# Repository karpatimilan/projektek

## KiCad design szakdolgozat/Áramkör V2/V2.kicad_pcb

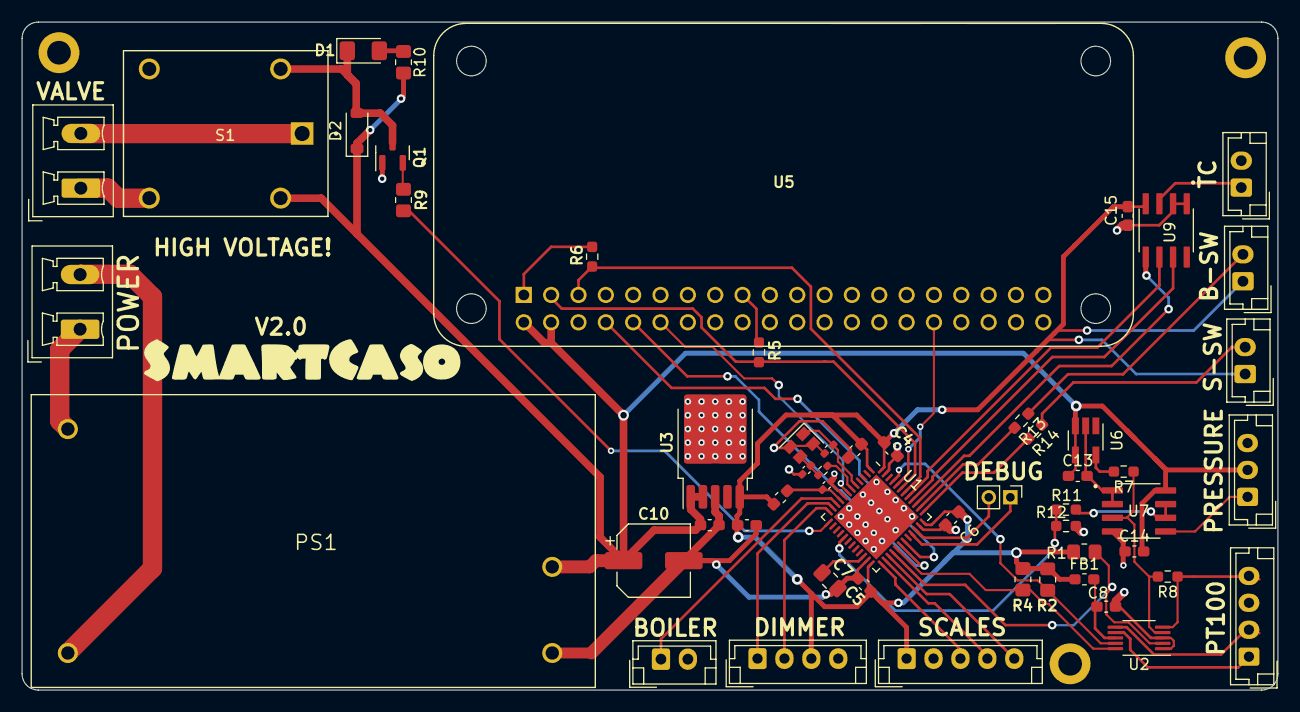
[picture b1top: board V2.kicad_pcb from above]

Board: 2 copper layers, 116.7 x 62.1 mm, 58 parts (1 on the bottom side), 52 nets.

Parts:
C1, C4, C5, C6, C8, C14: 100nF; C_0603_1608Metric_Pad1.08x0.95mm_HandSolder
C2, C3: 10pF; C_0402_1005Metric_Pad0.74x0.62mm_HandSolder
C7: 2.2uF; C_0805_2012Metric_Pad1.18x1.45mm_HandSolder
C9: 100nF; C_0402_1005Metric_Pad0.74x0.62mm_HandSolder
C10: C_Polarized_Small; CP_Elec_6.3x9.9
C11: 1uF; C_0603_1608Metric_Pad1.08x0.95mm_HandSolder
C12, C13: 47uF; C_0603_1608Metric_Pad1.08x0.95mm_HandSolder
C15: 0.1uF; C_0603_1608Metric_Pad1.08x0.95mm_HandSolder
D1: LED; LED_1206_3216Metric_Pad1.42x1.75mm_HandSolder
D2: 1N4148; D_SOD-123
FB1, FB2: FerriteBead; L_0603_1608Metric_Pad1.05x0.95mm_HandSolder
H1, H2, H3: MountingHole; MountingHole_2.2mm_M2_DIN965_Pad
J1: PT100; JST_EH_B4B-EH-A_1x04_P2.50mm_Vertical
J2: POWER; PhoenixContact_MCV_1,5_2-G-5.08_1x02_P5.08mm_Vertical
J3: VALVE; PhoenixContact_MCV_1,5_2-G-5.08_1x02_P5.08mm_Vertical
J4: THERMOCOUPLE; JST_EH_B2B-EH-A_1x02_P2.50mm_Vertical
J5: BOILER; JST_EH_B2B-EH-A_1x02_P2.50mm_Vertical
J6: Pressure; JST_EH_B3B-EH-A_1x03_P2.50mm_Vertical
J7: SCALES; JST_EH_B5B-EH-A_1x05_P2.50mm_Vertical
J8: DIMMER; JST_EH_B4B-EH-A_1x04_P2.50mm_Vertical
J9: DEBUG; PinHeader_1x02_P2.00mm_Vertical
J10: BREW_SWITCH; JST_EH_B2B-EH-A_1x02_P2.50mm_Vertical
J11: STEAM_SWITCH; JST_EH_B2B-EH-A_1x02_P2.50mm_Vertical
PS1: IRM-15-5; CONV_IRM-15-5
Q1: S8050; SOT-23
R1, R2, R4: 10K; R_0805_2012Metric_Pad1.20x1.40mm_HandSolder
R3: 0R; R_0402_1005Metric_Pad0.72x0.64mm_HandSolder
R5, R6, R7: 3.3K; R_0603_1608Metric_Pad0.98x0.95mm_HandSolder
R8: 100R; R_0603_1608Metric_Pad0.98x0.95mm_HandSolder
R9, R10: 1K; R_0805_2012Metric_Pad1.20x1.40mm_HandSolder
R11: 620; R_0603_1608Metric_Pad0.98x0.95mm_HandSolder
R12: 330; R_0603_1608Metric_Pad0.98x0.95mm_HandSolder
R13, R14: 1K; R_0603_1608Metric_Pad0.98x0.95mm_HandSolder
S1: JQC-3FF-S-Z; SW_JQC-3FF-S-Z
U1: STM32F411CEUx; QFN-48-1EP_7x7mm_P0.5mm_EP5.6x5.6mm
U2: ADS1115IDGST; VSSOP-10_3x3mm_P0.5mm
U3: TPS7B8633QKVURQ1; TO-252-5_TabPin6
U5: RASPBERRY_PI_ZERO_2_W; MODULE_RASPBERRY_PI_ZERO_2_W
U6: PREF4132B33DBVRQ1; SOT-23-5_HandSoldering
U7: LMC6482AIMX_NOPB; LMC6482
U9: MAX6675ISA_; MAX6675
Y1: 25 Mhz; Oscillator_SMD_SeikoEpson_SG210-4Pin_2.5x2.0mm

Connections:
+5V: C10.1, C11.1, C13.1, C14.2, D2.1 (K), J6.2, PS1.+V, R10.1, S1.5, U3.1 (VI), U3.2 (EN), U5.2 (5V_2), U5.4 (5V_4), U6.3 (EN), U6.4 (VIN), U7.8 (V+)
/3.3V: C1.1, C4.1, C5.1, C6.1, C12.1, C15.2, FB1.1, FB2.1, J7.1, J8.3, J10.1, J11.1, R1.2, R2.2, R4.2, U1.1 (VBAT), U1.24 (VDD), U1.36 (VDD), U1.48 (VDD), U3.5 (VO), U9.4 (VCC)
/+T: J4.1, U9.3 (T+)
/ALERT_RDY: R1.1, U1.28 (PB15), U2.2 (ALERT_RDY)
/AN0: R7.1, R8.2, U2.4 (AIN0), U7.3 (POSA)
/AN1: J1.4, R8.1, U2.5 (AIN1)
/AN2: J1.2, U2.6 (AIN2)
/AN3: J1.1, U2.7 (AIN3)
/BOILER_PWM: J5.1, U1.10 (PA0)
/Brew_Switch: R13.2, U1.38 (PA15)
/DIMMER_PWM: J8.1, U1.11 (PA1)
/HX711_1_DATA: J7.4, U1.26 (PB13)
/HX711_2_DATA: J7.5, U1.27 (PB14)
/HX711_SCK: J7.3, U1.25 (PB12)
/L: J3.1, S1.4
/MCU_OSC_IN: C2.2, U1.5 (PH0), Y1.1
/MCU_OSC_OUT: R3.1, U1.6 (PH1)
/NEGA: C13.2, U6.2 (GND), U7.1 (OUTA), U7.2 (NEGA)
/NEGB: R11.1, U7.6 (NEGB), U7.7 (OUTB)
/POSB: J6.1, U7.5 (POSB)
/POWER_L: J2.1, PS1.AC/L
/POWER_N: J2.2, PS1.AC/N
/RPI 3.3V: R5.2, R6.2, U5.1 (3V3_1), U5.17 (3V3_17)
/Relay: R9.2, U1.13 (PA3)
/STM32-ADS_SCL: R4.1, U1.29 (PA8), U2.10 (SCL)
/STM32-ADS_SDA: R2.1, U1.45 (PB8), U2.9 (SDA)
/STM32-MAX6675_CS: U1.41 (PB5), U9.6 (~CS)
/STM32-MAX6675_MISO: U1.40 (PB4), U9.7 (SO)
/STM32-MAX6675_SCK: U1.39 (PB3), U9.5 (SCK)
/STM32-RASPBERRY_SCL: R6.1, U1.42 (PB6), U5.5 (GPIO3/SCL)
/STM32-RASPBERRY_SDA: R5.1, U1.43 (PB7), U5.3 (GPIO2/SDA1)
/STM32_BOOT: U1.44 (BOOT0), U5.32 (GPIO12)
/STM32_RESET: U1.7 (NRST), U5.12 (GPIO18/GPIO_GEN1)
/STM32_RX-RPI_TX: U1.31 (PA10), U5.8 (GPIO14/TXD0)
/STM32_TX-RPI_RX: U1.30 (PA9), U5.10 (GPIO15/RXD0)
/SWCLK: J9.1, U1.33 (PA12)
/SWDIO: J9.2, U1.34 (PA13)
/Scaled_Pressure: R11.2, R12.1, U1.17 (PA7)
/Steam_Switch: R14.2, U1.37 (PA14)
/VREF: C9.1, FB2.2, U1.9 (VDDA)
/Valve: J3.2, S1.1
/XTAL_IN: C3.1, R3.2, Y1.3
/ZC_DIMMER: J8.2, U1.12 (PA2)
GND: C1.2, C2.1, C3.2, C4.2, C5.2, C6.2, C7.2, C8.2, C9.2, C10.2, C11.2, C12.2, C14.1, C15.1, J1.3, J4.2, J5.2, J6.3, J7.2, J8.4, PS1.-V, Q1.1 (E), R12.2, U1.8 (VSSA), U1.23 (VSS), U1.35 (VSS), U1.47 (VSS), U1.49 (VSS), U2.1 (ADDR), U2.3 (GND), U3.3 (GND), U5.6 (GND_6), U7.4 (V-), U9.1 (GND), U9.2 (T-), Y1.2, Y1.4
unnamed: D1.2 (A), R10.2
unnamed: D1.1 (K), D2.2 (A), Q1.3 (C), S1.2
unnamed: J10.2, R13.1
unnamed: J11.2, R14.1
unnamed: Q1.2 (B), R9.1
unnamed: C7.1, U1.22 (VCAP1)
unnamed: C8.1, FB1.2, U2.8 (VDD)
unnamed: R7.2, U6.5 (VREF)

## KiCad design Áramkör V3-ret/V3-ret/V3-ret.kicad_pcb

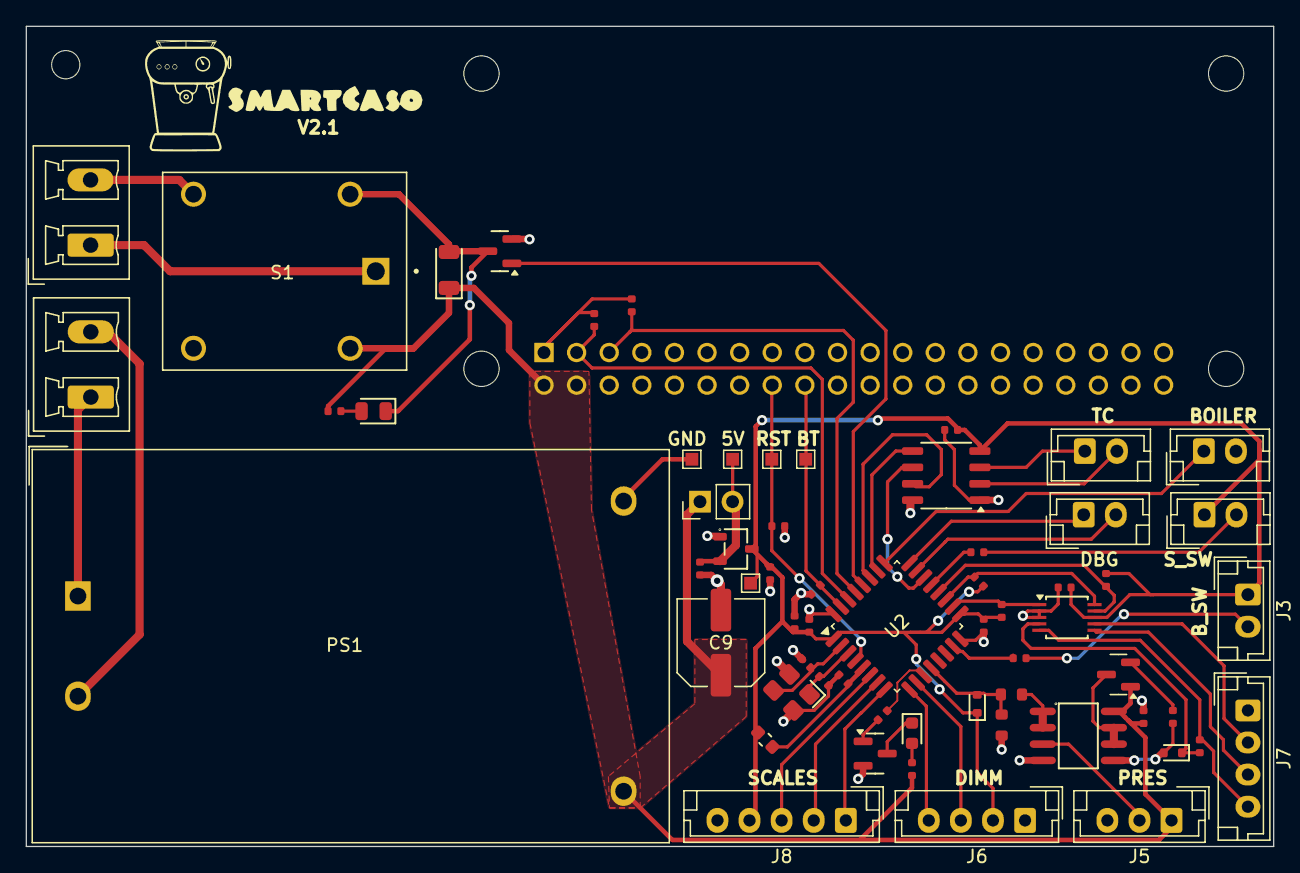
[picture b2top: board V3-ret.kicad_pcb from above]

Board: 2 copper layers, 97.2 x 63.9 mm, 64 parts (1 on the bottom side), 52 nets.

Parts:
5V1: TestPoint; TestPoint_Pad_1.0x1.0mm
C1, C5, C6, C11, C12, C13: 100nF; C_0402
C2, C3: 10pF; C_0402
C4, C8: 1uF; C_0402
C7: 4.7uF; C_0402
C9: C_Polarized; C_Elec_6.3x7.7
C10: 10nF; C_0402
D1: Green; D_0603
D2: Green; D_0805
D3: SM4007PL; D_SOD-123FL
D6, D7: 1SS389; D_SOD-523
FB1: FB_0603
GND1: TestPoint; TestPoint_Pad_1.0x1.0mm
H2: MountingHole; MountingHole_2.2mm_M2
J1, J2: Conn_01x02; PhoenixContact_MCV_1,5_2-G-5.08_1x02_P5.08mm_Vertical
J3, J4, J9, J11, J12: Conn_01x02; JST_EH_B2B-EH-A_1x02_P2.50mm_Vertical
J5: Conn_01x03; JST_EH_B3B-EH-A_1x03_P2.50mm_Vertical
J6, J7: Conn_01x04; JST_EH_B4B-EH-A_1x04_P2.50mm_Vertical
J8: Conn_01x05; JST_EH_B5B-EH-A_1x05_P2.50mm_Vertical
JPr1: Jumper_2_Open; PinHeader_1x02_P2.54mm_Vertical
PS1: HLK-10M05; Converter_ACDC_Hi-Link_HLK-10Mxx
Q1, Q2: 2N7002; Q_SOT-23
R1: 10kΩ; R_0402
R2: 100Ω; R_0402
R3, R4, R5, R15, R16: 1kΩ; R_0402
R6, R7, R8, R18, R19: 3.3kΩ; R_0402
R17: 820Ω; R_0603
R20: 300Ω; R_0603
R21: 2.4kΩ; R_0402
S1: JQC-3FF-S-Z; SW_JQC-3FF-S-Z
TP1, TP2, TP3: TestPoint; TestPoint_Pad_1.0x1.0mm
U1: XC6206P332MR; SOT-23-3_L2.9-W1.6-P1.90-LS2.8-BR
U2: STM32F301K8Tx; LQFP-32_7x7mm_P0.8mm
U3: MCP6002T; SOIC-8_L4.9-W3.9-P1.27-LS6.0-BL
U4: RASPBERRY_PI_ZERO_2_W; MODULE_RASPBERRY_PI_ZERO_2_W
U5: ADS1115IDGS; TSSOP-10_3x3mm_P0.5mm
U9: MCP1525-TT; SOT-23
U10: MAX6675ISA_; SOIC-8_3.9x4.9mm_P1.27mm
X1: X322525MOB4SI; OSC-SMD_4P-L3.2-W2.5-BL

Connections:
1mA_CURR_SRC: J7.4, R2.2, U5.5 (AIN1)
230V_L: J1.1, PS1.1 (AC/L)
230V_N: J1.2, PS1.2 (AC/N)
+3.3V: C5.1, C6.1, C7.1, C8.1, C11.1, C12.1, D6.1, FB1.2, J3.1, J4.1, J6.2, J8.4, R6.1, R7.1, R8.1, R18.2, R19.2, TP3.1, U1.3 (Vout), U2.1 (VDD), U2.17 (VDD), U4.1 (3V3_1), U4.17 (3V3_17), U5.8 (VDD), U10.4 (VCC)
+5V: C9.1, C13.1, D3.1, J5.1, JPr1.1 (A), PS1.4 (+Vout), R3.2, R5.1, S1.5, U3.8 (VDD), U4.2 (5V_2), U4.4 (5V_4), U9.1 (Vin)
/5V_JMPR: 5V1.1, C4.1, JPr1.2 (B), U1.2 (Vin)
/NEG_B: U3.6 (-INB), U3.7 (OUTB), U9.3 (Vss)
/POS_B: D7.2, R21.2, U3.5 (+INB)
ADC_SCL: R6.2, U2.19 (PA9), U5.10 (SCL)
ADC_SDA: R7.2, U2.20 (PA10), U5.9 (SDA)
ALERT_RDY: R8.2, U2.18 (PA8), U5.1 (ADDR)
AN0: D7.1, R2.1, U5.4 (AIN0)
AN2: J7.3, U5.6 (AIN2)
AN3: J7.2, U5.7 (AIN3)
BOILER_PWM: J9.1, U2.25 (PA15)
BOOT: R1.1, TP1.1, U2.31 (BOOT0), U4.18 (GPIO24/GPIO_GEN5)
BREW_SWITCH: R15.1, U2.15 (PB1)
DEBUG_CLK: J12.1, U2.24 (PA14)
DEBUG_SDA: J12.2, U2.23 (PA13)
DIMMER: J6.4, U2.9 (PA3)
DIMMER_ZC: J6.3, U2.10 (PA4)
GND: C1.1, C2.1, C3.1, C4.2, C5.2, C6.2, C7.2, C8.2, C9.2, C10.2, C11.2, C12.2, C13.2, GND1.1, J5.3, J6.1, J7.1, J8.5, J9.2, PS1.3 (-Vout), Q1.2 (S), Q2.2 (S), R1.2, R20.2, U1.1 (GND), U2.16 (VSS), U2.32 (VSS), U3.4 (-VSS), U4.6 (GND_6), U4.9 (GND_9), U4.14 (GND_14), U4.20 (GND_20), U4.25 (GND_25), U4.30 (GND_30), U4.34 (GND_34), U4.39 (GND_39), U5.2 (ALERT/RDY), U5.3 (GND), U10.1 (GND), U10.8 (N.C.), X1.2 (GND), X1.4 (GND)
HX711_D1: J8.2, U2.7 (PA1)
HX711_D2: J8.3, U2.6 (PA0)
HX711_SCL: J8.1, U2.8 (PA2)
LED: R4.1, U2.11 (PA5)
MAX6675_CS: U2.22 (PA12), U10.6 (~CS)
MAX6675_MISO: U2.27 (PB4), U10.7 (SO)
MAX6675_SCK: U2.26 (PB3), U10.5 (SCK)
unnamed: D1.2, R3.1
unnamed: D2.2, R5.2
unnamed: J3.2, R15.2
unnamed: J4.2, R16.2
unnamed: D2.1, D3.2, Q1.3 (D), S1.2
unnamed: D1.1, Q2.3 (D)
unnamed: Q2.1 (G), R4.2
unnamed: R17.1, U3.1 (OUTA), U3.2 (-INA)
unnamed: R21.1, U9.2 (Vout)
PRESSURE: J5.2, U3.3 (+INA)
RCC_OSC_IN: C2.2, U2.2 (PF0), X1.3 (OSC)
RCC_OSC_OUT: C3.2, U2.3 (PF1), X1.1 (OSC)
RELAY: Q1.1 (G), U2.28 (PB5)
RESET: C1.2, TP2.1, U2.4 (NRST), U4.16 (GPIO23/GPIO_GEN4)
RPI_SCL: R18.1, U2.29 (PB6), U4.5 (GPIO3/SCL)
RPI_SDA: R19.1, U2.30 (PB7), U4.3 (GPIO2/SDA1)
Relay_L1: J2.1, S1.1
Relay_L2: J2.2, S1.3
SCALED_PRESSURE: D6.2, R17.2, R20.1, U2.12 (PA6)
STEAM_SWITCH: R16.1, U2.21 (PA11)
T+: J11.1, U10.3 (T+)
T-: J11.2, U10.2 (T-)
VDDA: C10.1, FB1.1, U2.5 (VDDA)

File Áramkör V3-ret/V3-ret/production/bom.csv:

Designator,Footprint,Quantity,Value,LCSC Part #
"5V1, GND1, TP1, TP2, TP3",TestPoint_Pad_1.0x1.0mm,5,TestPoint,
"C1, C11, C12, C13, C5, C6",C_0402,6,100nF,C1525
C10,C_0402,1,10nF,C15195
"C2, C3",C_0402,2,10pF,C32949
"C4, C8",C_0402,2,1uF,C52923
C7,C_0402,1,4.7uF,C23733
C9,C_Elec_6.3x7.7,1,C_Polarized,
D1,D_0603,1,Green,C2986059
D2,D_0805,1,Green,C2297
D3,D_SOD-123FL,1,SM4007PL,C64898
"D6, D7",D_SOD-523,2,1SS389,C22466369
FB1,FB_0603,1,~,C1002
"J1, J2","PhoenixContact_MCV_1,5_2-G-5.08_1x02_P5.08mm_Vertical",2,Conn_01x02,
"J11, J12, J3, J4, J9",JST_EH_B2B-EH-A_1x02_P2.50mm_Vertical,5,Conn_01x02,
J5,JST_EH_B3B-EH-A_1x03_P2.50mm_Vertical,1,Conn_01x03,
"J6, J7",JST_EH_B4B-EH-A_1x04_P2.50mm_Vertical,2,Conn_01x04,
J8,JST_EH_B5B-EH-A_1x05_P2.50mm_Vertical,1,Conn_01x05,
JPR1,PinHeader_1x02_P2.54mm_Vertical,1,Jumper_2_Open,
PS1,Converter_ACDC_Hi-Link_HLK-10Mxx,1,HLK-10M05,
"Q1, Q2",Q_SOT-23,2,2N7002,C8545
R1,R_0402,1,10kΩ,C25744
"R15, R16, R3, R4, R5",R_0402,5,1kΩ,C11702
R17,R_0603,1,820Ω,C23253
"R18, R19, R6, R7, R8",R_0402,5,3.3kΩ,C25890
R2,R_0402,1,100Ω,C25076
R20,R_0603,1,300Ω,C23025
R21,R_0402,1,2.4kΩ,C25882
S1,SW_JQC-3FF-S-Z,1,JQC-3FF-S-Z,
U1,SOT-23-3_L2.9-W1.6-P1.90-LS2.8-BR,1,XC6206P332MR,C5446
U10,SOIC-8_3.9x4.9mm_P1.27mm,1,MAX6675ISA_,
U2,LQFP-32_7x7mm_P0.8mm,1,STM32F301K8Tx,
U3,SOIC-8_L4.9-W3.9-P1.27-LS6.0-BL,1,MCP6002T,C7377
U4,MODULE_RASPBERRY_PI_ZERO_2_W,1,RASPBERRY_PI_ZERO_2_W,
U5,TSSOP-10_3x3mm_P0.5mm,1,ADS1115IDGS,C37593
U9,SOT-23,1,MCP1525-TT,
X1,OSC-SMD_4P-L3.2-W2.5-BL,1,X322525MOB4SI,C9006

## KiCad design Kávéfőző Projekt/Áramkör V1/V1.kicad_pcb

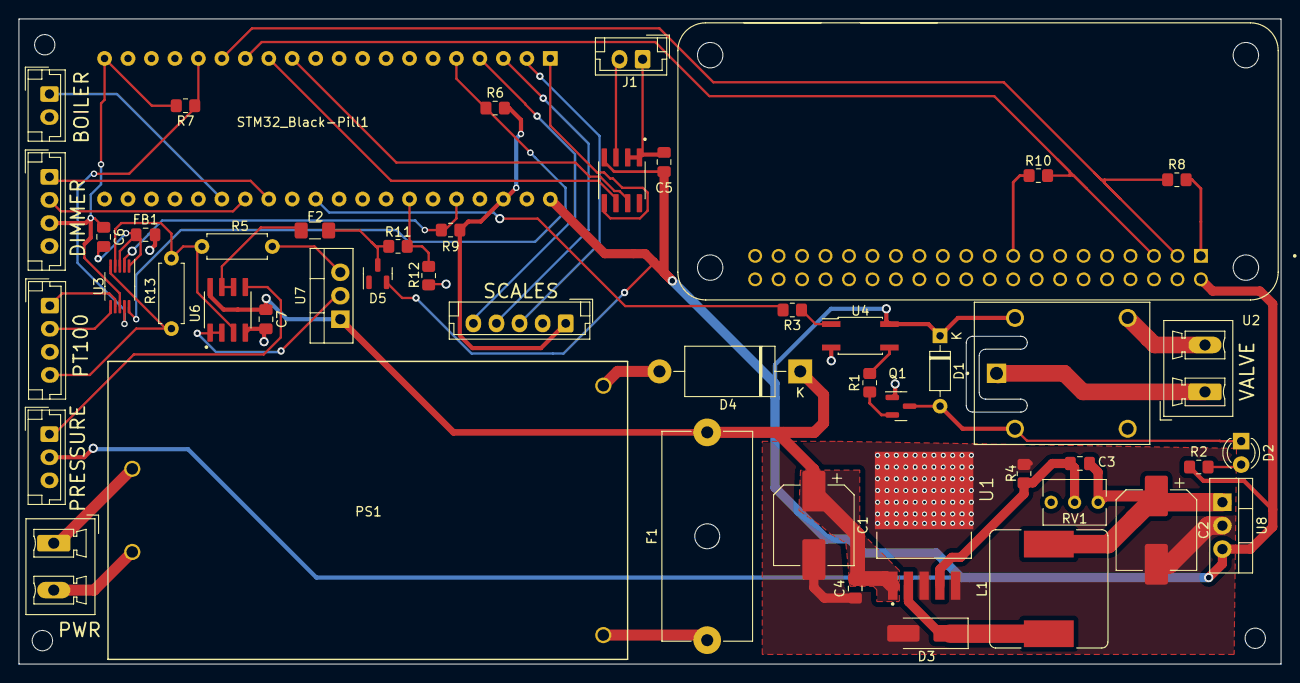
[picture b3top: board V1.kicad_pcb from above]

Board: 2 copper layers, 136.7 x 69.9 mm, 53 parts (0 on the bottom side), 44 nets.

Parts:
BOILER: Conn_01x02; JST_EH_B2B-EH-A_1x02_P2.50mm_Vertical
C1: 100uF; CP_Elec_8x10.5
C2: 220nF; CP_Elec_8x10.5
C3, C4, C6, C7: 100nF; C_0805_2012Metric_Pad1.18x1.45mm_HandSolder
C5: 0.1uF; C_0805_2012Metric_Pad1.18x1.45mm_HandSolder
D1: 1N4148; D_DO-35_SOD27_P7.62mm_Horizontal
D2: LED; LED_D3.0mm
D3: 1N5822; D_SMA_Handsoldering
D4: 1N53xxB; D_DO-201_P15.24mm_Horizontal
D5: BAT54A; SOT-23
DIMMER: Conn_01x04; JST_EH_B4B-EH-A_1x04_P2.50mm_Vertical
F1: Fuse; Fuseholder_Cylinder-5x20mm_Schurter_0031_8201_Horizontal_Op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
F2: Fuse; Fuse_1206_3216Metric_Pad1.42x1.75mm_HandSolder
FB1: FerriteBead; Fuse_0805_2012Metric_Pad1.15x1.40mm_HandSolder
H1, H2, H4: MountingHole; MountingHole_2.2mm_M2_DIN965
J1: Screw_Terminal_01x02; JST_EH_B2B-EH-A_1x02_P2.50mm_Vertical
J7: Conn_01x04; JST_EH_B4B-EH-A_1x04_P2.50mm_Vertical
L1: 47uH; L_Bourns_SRR1260
PRESSURE: Conn_01x03; JST_EH_B3B-EH-A_1x03_P2.50mm_Vertical
PS1: HLK-20M12; DIP4_HLK-20Mxx_HLK
PWR: Conn_01x02; PhoenixContact_MCV_1,5_2-G-5.08_1x02_P5.08mm_Vertical
Q1: S8050; SOT-23
R1, R2, R3: 1K; R_0805_2012Metric_Pad1.20x1.40mm_HandSolder
R4: 330R; R_0805_2012Metric_Pad1.20x1.40mm_HandSolder
R5: 10K; R_Axial_DIN0207_L6.3mm_D2.5mm_P7.62mm_Horizontal
R6, R7, R9: 10K; R_0805_2012Metric_Pad1.20x1.40mm_HandSolder
R8, R10: 3.3K; R_0805_2012Metric_Pad1.20x1.40mm_HandSolder
R11: 620; R_0805_2012Metric_Pad1.20x1.40mm_HandSolder
R12: 330; R_0805_2012Metric_Pad1.20x1.40mm_HandSolder
R13: 1K; R_Axial_DIN0207_L6.3mm_D2.5mm_P7.62mm_Horizontal
RV1: R_Potentiometer; Potentiometer_Vishay_T73XW_Horizontal
S1: JQC-3FF-S-Z; SW_JQC-3FF-S-Z
SCALES: Conn_01x05; JST_EH_B5B-EH-A_1x05_P2.50mm_Vertical
STM32_Black-Pill1: STM32-BlackPill
U1: LM2596DSADJG; CONV_LM2596DSADJG
U2: RASPBERRY_PI_ZERO_2_W; MODULE_RASPBERRY_PI_ZERO_2_W
U3: ADS1115IDGST; VSSOP-10_3x3mm_P0.5mm
U4: LTV-354T; SO-4_4.4x3.6mm_P2.54mm
U5: MAX6675ISA_; MAX6675
U6: LMC6482AIMX_NOPB; LMC6482
U7: LM7810_TO220; TO-220-3_Vertical
U8: LF50_TO220; TO-220-3_Vertical
VALVE: Screw_Terminal_01x02; PhoenixContact_MCV_1,5_2-G-5.08_1x02_P5.08mm_Vertical

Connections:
/3.3V: C6.1, DIMMER.3, R6.2, R7.2, R9.2, SCALES.1, STM32_Black-Pill1.20 (3.3V), STM32_Black-Pill1.23 (3.3V), U3.8 (VDD)
/5.5V: C2.1, C3.2, L1.2, RV1.1, U8.1 (VI)
/5V: C5.2, D1.1 (K), D5.2, PRESSURE.2, R2.1, S1.5, STM32_Black-Pill1.21 (5V), U2.2 (5V_2), U4.4, U5.4 (VCC), U8.3 (VO)
/ALERT_RDY: R9.1, STM32_Black-Pill1.25 (PB2), U3.2 (ALERT_RDY)
/AN0: R5.1, R13.2, U3.4 (AIN0), U6.3 (POSA)
/AN1-AN2: J7.2, J7.4, R13.1, U3.5 (AIN1), U3.6 (AIN2)
/AN3MEASURE: J7.1, U3.7 (AIN3)
/BOILER_PWM: BOILER.1, STM32_Black-Pill1.35 (PA0)
/DIMMER_PWM: DIMMER.1, STM32_Black-Pill1.33 (PA2)
/HX711_1_DATA: SCALES.4, STM32_Black-Pill1.3 (PB14)
/HX711_2_DATA: SCALES.5, STM32_Black-Pill1.4 (PB15)
/HX711_SCK: SCALES.3, STM32_Black-Pill1.2 (PB13)
/L: S1.4, VALVE.2
/Pressure: PRESSURE.1, U6.5 (POSB)
/Pressure_OUTPUT: F2.2, U6.6 (NEGB), U6.7 (OUTB)
/RPI 3.3V: R8.2, R10.2, U2.1 (3V3_1), U2.17 (3V3_17)
/Relay: R3.2, STM32_Black-Pill1.31 (PA4)
/STM32-ADS_SCL: R6.1, STM32_Black-Pill1.5 (PA8), U3.10 (SCL)
/STM32-ADS_SDA: R7.1, STM32_Black-Pill1.16 (PB8), U3.9 (SDA)
/STM32-MAX6675_CS: STM32_Black-Pill1.13 (PB5), U5.6 (~CS)
/STM32-MAX6675_MISO: STM32_Black-Pill1.12 (PB4), U5.7 (SO)
/STM32-MAX6675_SCK: STM32_Black-Pill1.1 (PB12), U5.5 (SCK)
/STM32-RASPBERRY_SCL: R10.1, STM32_Black-Pill1.14 (PB6), U2.5 (GPIO3/SCL)
/STM32-RASPBERRY_SDA: R8.1, STM32_Black-Pill1.15 (PB7), U2.3 (GPIO2/SDA1)
/Scaled_Pressure: R11.2, R12.1, STM32_Black-Pill1.27 (PB0)
/ZC_DIMMER: DIMMER.2, STM32_Black-Pill1.34 (PA1)
GND: BOILER.2, C1.2, C2.2, C4.1, C5.1, C7.1, D3.2 (A), D4.2 (A), DIMMER.4, FB1.2, J1.1, J7.3, PRESSURE.3, PS1.3 (-VO), Q1.1 (E), R4.1, R12.2, SCALES.2, STM32_Black-Pill1.22 (GND), U1.3 (GROUND), U1.5 (~ON/OFF), U1.6 (EXP), U2.6 (GND_6), U4.2, U5.1 (GND), U5.2 (T-), U6.4 (V-), U8.2 (GND)
unnamed: D1.2 (A), D2.1 (K), Q1.3 (C), S1.2
unnamed: D2.2 (A), R2.2
unnamed: D3.1 (K), L1.1, U1.2 (OUTPUT)
unnamed: D5.3, F2.1, R11.1
unnamed: J1.2, U5.3 (T+)
unnamed: S1.1, VALVE.1
unnamed: PS1.1 (AC(L)), PWR.1
unnamed: PS1.2 (AC(N)), PWR.2
unnamed: F1.1, PS1.4 (+VO)
unnamed: Q1.2 (B), R1.1
unnamed: R1.2, U4.3
unnamed: R3.1, U4.1
unnamed: C3.1, R4.2, RV1.2, U1.4 (FEEDBACK)
unnamed: C6.2, FB1.1, U3.1 (ADDR), U3.3 (GND)
unnamed: U6.1 (OUTA), U6.2 (NEGA), U7.2 (GND)
unnamed: R5.2, U7.3 (VO)
VCC: C1.1, C4.2, C7.2, D4.1 (K), F1.2, U1.1 (VIN), U6.8 (V+), U7.1 (VI)
